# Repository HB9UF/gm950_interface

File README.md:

This is a simple interface that plugs into the back of Motorola GM950 radios to break out:

- Flat RX audio
- Flat TX audio
- The PTT line
- Open collector COS or TOS (depending on configuration)

The intended use for this project is to connect a link transceiver to the  EchoLink network. The interface was designed for the GM950 series but may also work with GM350 (untested). It was designed with KiCad 5.1.5 as a quick replacement for a failed unit. The first version was milled in-house during the COVID-19 lock-down, thus traces are extra wide and on a single layer to ease the manufacturing process.

This is provided as is under the CC BY-SA 4.0 license. In particular, no BOM is provided but the schematic is straight forward. SMD component sizes are 0805. Please refer to the schematic for modification of the suggested resistor values, depending on your application.

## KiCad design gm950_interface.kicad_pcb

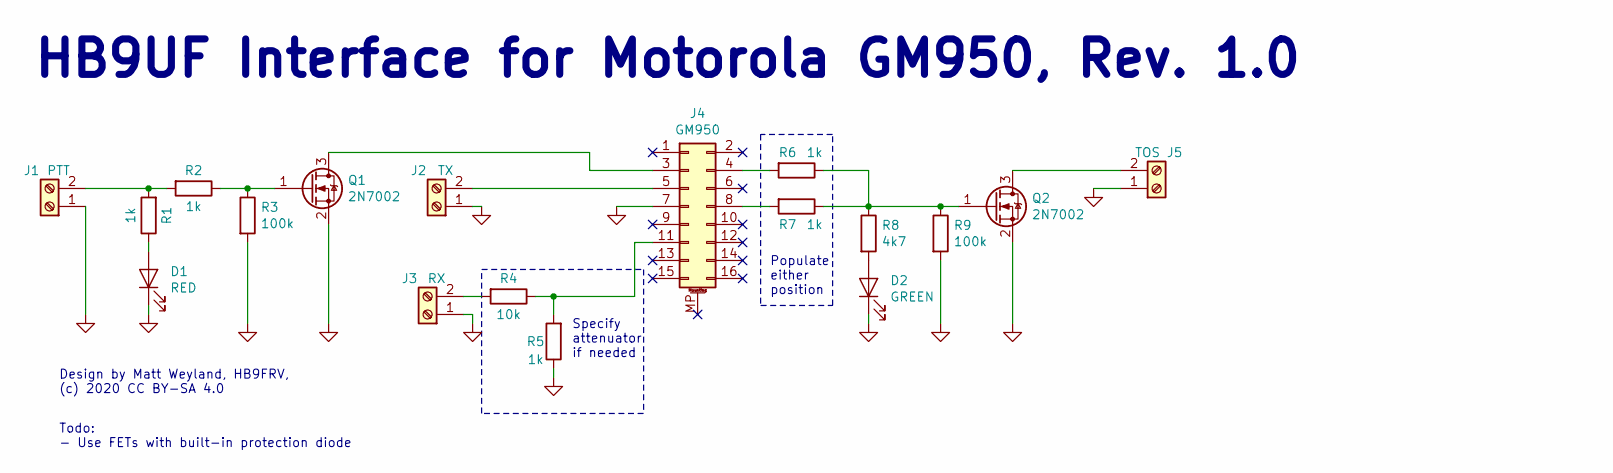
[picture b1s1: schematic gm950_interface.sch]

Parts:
D1: RED; LED_0805_2012Metric_Pad1.15x1.40mm_HandSolder
D2: GREEN; LED_0805_2012Metric_Pad1.15x1.40mm_HandSolder
J1: PTT; TerminalBlock_TE_282834-2_1x02_P2.54mm_Horizontal
J2: TX; TerminalBlock_TE_282834-2_1x02_P2.54mm_Horizontal
J3: RX; TerminalBlock_TE_282834-2_1x02_P2.54mm_Horizontal
J4: GM950; PinSocket_2x08_P2.54mm_Vertical
J5: TOS; TerminalBlock_TE_282834-2_1x02_P2.54mm_Horizontal
Q1, Q2: 2N7002; SOT-23
R1, R2, R5, R6, R7: 1k; R_0805_2012Metric_Pad1.15x1.40mm_HandSolder
R3, R9: 100k; R_0805_2012Metric_Pad1.15x1.40mm_HandSolder
R4: 10k; R_0805_2012Metric_Pad1.15x1.40mm_HandSolder
R8: 4k7; R_0805_2012Metric_Pad1.15x1.40mm_HandSolder

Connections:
GND: D1.1 (K), D2.1 (K), J1.1, J2.1, J3.1, J4.7, J5.1, Q1.2 (S), Q2.2 (S), R3.2, R5.1, R9.2
unnamed: D1.2 (A), R1.1
unnamed: D2.2 (A), R8.2
unnamed: J1.2, R1.2, R2.2
unnamed: J2.2, J4.5
unnamed: J3.2, R4.2
unnamed: J4.3, Q1.3 (D)
unnamed: J4.4, R6.2
unnamed: J4.8, R7.2
unnamed: J4.11, R4.1, R5.2
unnamed: J5.2, Q2.3 (D)
unnamed: Q1.1 (G), R2.1, R3.1
unnamed: Q2.1 (G), R6.1, R7.1, R8.1, R9.1

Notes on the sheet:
Todo: - Use FETs with built-in protection diode
Design by Matt Weyland, HB9FRV, (c) 2020 CC BY-SA 4.0
HB9UF Interface for Motorola GM950, Rev. 1.0
Specify attenuator if needed
Populate either position

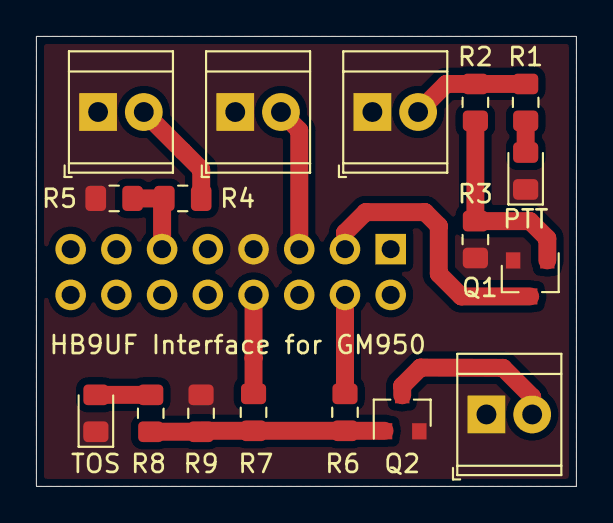
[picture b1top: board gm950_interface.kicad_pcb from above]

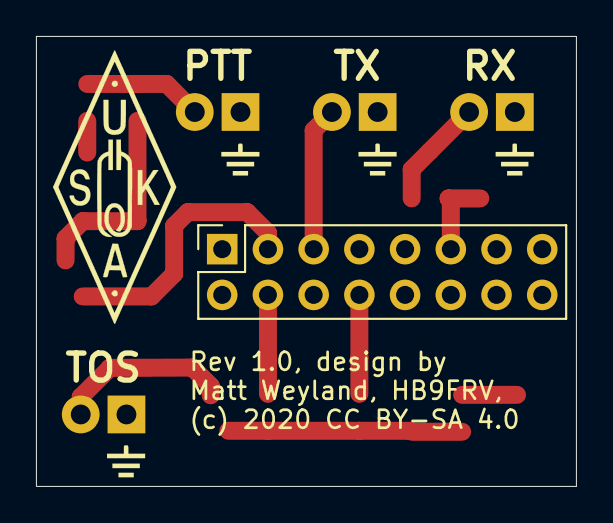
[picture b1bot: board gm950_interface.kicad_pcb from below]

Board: 2 copper layers, 30.0 x 25.0 mm, 22 parts (5 on the bottom side), 13 nets.

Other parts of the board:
VAL: GND
VAL#2, VAL#3, VAL#4: GND

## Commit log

2020-04-05 Initial commit of rev. 1.0
2020-04-05 Adding .gitignore file for KiCad projects.
2020-04-05 Adding images of schematic and rendering of PCB, included in README.md file
2020-09-21 Bumping KiCad version number. This is the Rev. 1.0 release.
